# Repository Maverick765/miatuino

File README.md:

# Miatuino ECU NA6 PNP

MiatuinoはSpeeduinoをベースとしたNA6ロードスター専用ECUプロジェクトです。

Speeduino MX-5 PNPモデルをベースとし、部品の入手性、組み立てやすさなどを改善しました。

基本的な技術情報については公式のWikiを参照してください。
https://wiki.speeduino.com

また、部品に関してはできる限り日本国内で入手しやすいものにしています。国内で入手できないものはAliexpressやLCSCで入手可能です。

---

## 対応車種

- 車種：ユーノス・ロードスター（NA6CE）
- 年式：1989年〜1995年
- エンジン：1.6L B6ZE(RS)

注意：NA8には対応していません。

---

## Speeduinoからの変更点

- Arduino Mega2560をMega2560 Proに変更
- SMD部品を減らし、手はんだで組み立てやすいように変更
- A/C制御回路の追加
- 電源回路をROHM製のDC-DCコンバータBP5293-50に変更
- MAPセンサをBOSCH製0 281 002 593に変更

---

## 注意事項

- 仕様はほぼSpeeduinoと同様です。詳細仕様は [Speeduino公式Wiki](https://wiki.speeduino.com/) を参照してください。
- 純正には**吸気温センサー（IAT）が存在しない**ため、追加設置が必須です。
- ノック制御、スピードセンサーなどには非対応です。

---

## ECUの組み立てと取付に必要なもの

- Miatuino基板  
リポジトリ内のGerberファイルを利用。
- 実装用部品  
リポジトリ内の部品表を参照。
- 吸気温センサー(IAT)  
品番：25036751  
エアフロメーターを外したカプラに接続します。  
Aliexpressなどで入手可能
- 吸気温センサー用カプラ  
Aliexpressで「7pin Automotive Connector」などと検索すれば見つかります。
- スロットルポジションセンサー(TPS)  
品番：0280122001  
カプラの形状と配線が純正と同じため、そのまま利用できます。  
Aliexpressなどで入手可能。
- スロットルポジションセンサー用マウントアダプター  
リポジトリ内の.stlファイルを利用。  
3Dプリンタで出力するか、3Dプリントサービスを利用してください。  
.stlファイルは以下のページからも入手可能です。  
[1.6 Miata Kia type tps adapter M5 nuts](https://www.thingiverse.com/thing:4611603)
- MAPセンサー  
0 281 002 593  
Aliexpressなどで入手可能。
- MAPセンサー用カプラー  
品番：1928403966  
Aliexpressなどで入手可能。
- 基板用ケース  
基板のサイズは100mm x 100mmです。適当なサイズのアルミケースに入れます。
- 基板用USB Type Cコネクタ  
ケース内のMega 2560 Proと接続するためのパネルマウントのType Cコネクタ。
- 内径4.5mmのホース   
3m程度。キジマのガソリンホースがおススメです。
- TunerStudio  
[公式ページ](https://www.efianalytics.com/TunerStudio/)から入手可能。
- SpeedyLoader  
[公式ページ](https://speeduino.com/home/support/downloads)から入手可能。

---

## 製作

基本的にはKiCADのプロジェクトや部品表を見ながらはんだ付けすればOKです。
MAPセンサーは基板の3ピンコネクタにカプラを介して取り付けます。

---

## ファームウェアの書き込み

SpeedyLoaderを利用してファームウェアを書き込みます。
[SpeedyLoaderの公式マニュアル](https://wiki.speeduino.com/en/Installing_Firmware)を参考にしてください。

また、書き込みが完了したらbase tuneをダウンロードしておきます。

---

## 取付手順

### スロットルポジションセンサーを交換する

純正のスロットルポジションセンサーを外し、新しいスロットルポジションセンサーをアダプターを利用して取り付けます。

なお、純正のセンサーを取り外すには、スロットルボディーを外す必要があります。
(純正のセンサーを破壊すればスロットルボディーを外さずに新しいセンサーを取り付けることも可能ですがおススメしません)

### エアフロメーターのカプラを外して吸気温センサーを取り付ける

エアフロメータにつながっている7ピンのカプラを外し、吸気温センサを取り付けます。

### ST-SIGのヒューズを外す

エンジンルーム内の運転席側のヒューズボックスを開け、ST-SIGのヒューズを外します。
なお、Miatuinoを利用する場合、このヒューズは常に外したままにしておく必要があります。

_ST-SIGのヒューズは、セルモーターを回している間、一時的に燃料ポンプを動かすための電源が来ているヒューズです。_
_純正状態のNA6では、燃料ポンプの電源ON/OFFをフラップ式のエアフロメータの中にある機械式の接点で行っています。つまり、エンジンが回って負圧が発生している状態でないと燃料ポンプは作動しません。_
_エンジン始動時は負圧が弱く、この接点が動かないため、一時的に燃料ポンプに電源を供給する必要があります。その電源が来ているのがST-SIGのヒューズです。_
_Miatuinoでは、エアフロメータの配線を流用して燃料ポンプの制御を行うことになりますが、この時、ST-SIGのヒューズを残したままにしていると、キーを回したときに基板のドライバICに電流が逆流し、基板が焼けます。_

### 純正ECUを取り外す

助手席側スカッフプレート、一部のトリムを外してカーペットをめくります。
スチールのカバーパネルを外すと、ステーで固定されたECUが見えるので取り外し、カプラーを外します。

### MAPセンサーへつなぐホースを通す

MiatuinoではDジェトロニック方式になるため、インテークマニホールドの負圧をホースでECUまで接続する必要があります。
純正のインテークマニホールドには、ゴムキャップが付いた使われていない負圧取り出しニップルがあるので、それを利用します。
また、ロードスターのエンジンルーム隔壁にはゴム栓でメクラされた穴があるので、その栓を外してホースを通します。

カーペットをめくっている間に、エンジンルーム側からホースを送り、室内側の足元まで届かせます。
室内と反対側のホースの先をインマニにあるニップルに取り付けます。

### Miatuinoを取り付ける

純正ECUを取り外したカプラと、先ほど通したホースをMiatuinoに繋ぎます。
ECUのセッティングやトラブルシューティングのためにも、ECUは元の場所に戻さず、助手席足元に転がすなりしておきます。
ECU底面に面ファスナーのテープを取り付け、内装に張り付けておくのもおすすめです。

---

## セットアップ手順

PCとMiatuinoをUSBケーブルで接続し、PCでTuner Studioを起動し、初期データの書き込みと各種センサーのキャリブレーションを行います。

#### 初期データの書き込み

SpeedyLoaderからダウンロードしたbase tuneを書き込みます。

[File] -> [Load Tune(MSQ)]を選択して、SpeedyLoaderでからダウンロードしたbase tuneを書き込みます。

#### TPSのキャリブレーション

[Tools] -> [Calibrate TPS]を選択します。

正しくTPSが接続されていれば、アクセルペダルを踏めば値が変化することを確認できます。

まずはアクセルを完全に戻した状態で[Closed throttle ADC Count]の右の[Get Current]をクリックして、スロットル全閉時の値を取得します。
次に、アクセルを完全に踏み込んだ状態で[Full throttle ADC Count]の右の[Get Current]をクリックして、スロットル前回時の値を取得します。
完了したら[Accept]をクリックします。

この際、センサーの極性(全開で0Vか、全閉で0Vか)で警告が出ることがありますが、そのまま進めればSpeeduino側で勝手に極性を変更してくれます。

#### 水温センサーのキャリブレーション

[Tools] -> [Calibrate Tempereture Sensor]を選択します。

[SensorTable]のプルダウンから[Coolant Tempereture Sensor]を選択します。

[Table Input Solution]が3 Point Therm Generatorになっていることを確認します。

[Common Sensor Values]のプルダウンから[RX7_CLT(S4&S5)]を選択します。

[Write to Controller]をクリックして完了したら[Close]をクリックします。

#### 吸気温センサーのキャリブレーション

[Tools] -> [Calibrate Tempereture Sensor]を選択します。

[SensorTable]のプルダウンから[Air Tempereture Sensor]を選択します。

[Table Input Solution]が3 Point Therm Generatorになっていることを確認します。

[Common Sensor Values]のプルダウンから[RX7_AFM(S5 in AFM)]を選択します。

[Write to Controller]をクリックして完了したら[Close]をクリックします。

#### O2センサーの設定

[Tuning] -> [AFR/O2]を選択します。

純正のO2センサーを利用する場合、[Sensor Type]に[Narrow Band]を指定します。

完了したら[Burn]をクリックして[Close]をクリックします。

純正のO2センサーを利用する場合はこれで完了ですが、社外のワイドバンドセンサーを付けている場合はキャリブレーションを行う必要があります。

[Tools] -> [Calibrate AFR Sensor]を選択します。

[EGO Sensor]のプルダウンメニューから、利用しているセンサーのメーカーを選択します。

[Write to Controller]をクリックして完了したら[Close]をクリックします。

---

## 関連リンク

- [Speeduino 公式サイト（英語）](https://speeduino.com/)
- [Speeduino Wiki（英語）](https://wiki.speeduino.com/en/boards/MX5_PNP)
- [TunerStudio ダウンロードページ](https://www.efianalytics.com/TunerStudio/)
- [Speedy Loader ダウンロードページ](https://speeduino.com/home/support/downloads)
- [1.6 Miata Kia type tps adapter M5 nuts](https://www.thingiverse.com/thing:4611603)

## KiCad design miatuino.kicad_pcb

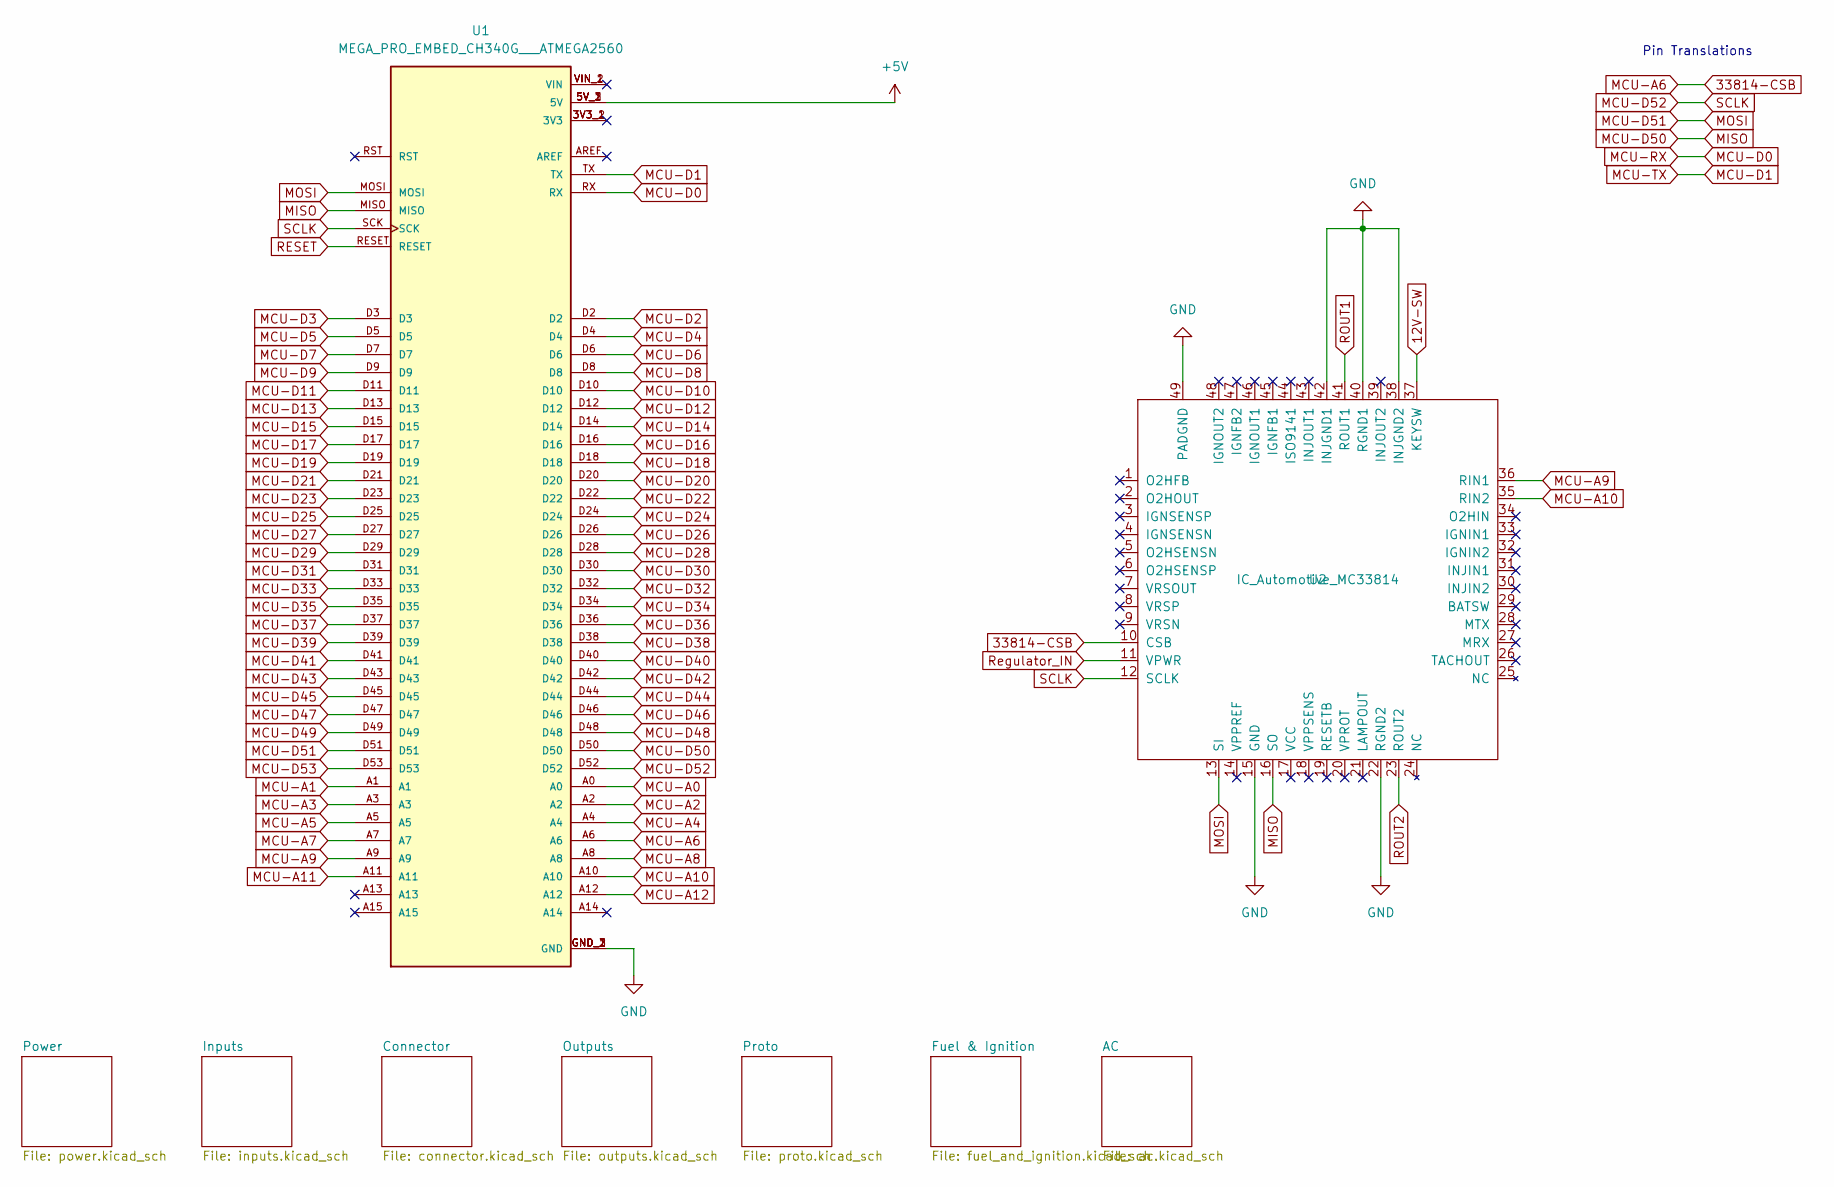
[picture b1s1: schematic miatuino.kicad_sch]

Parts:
U1: MEGA_PRO_EMBED_CH340G___ATMEGA2560; Arduino Mega Pro; PARTREV 12/May/2017
U2: IC_Automotive_MC33814; LQFP-48-1EP_7x7mm_P0.5mm_EP3.6x3.6mm_ThermalVias; Manufacturer_Part_Number MC33814

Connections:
12V-SW: U2.37 (KEYSW); also elsewhere on the board
33814-CSB: U1.A6, U2.10 (CSB)
+5V: U1.5V_1 (5V), U1.5V_2 (5V), U1.5V_3 (5V); also elsewhere on the board
ADC-Clamp-1: U1.A0; also elsewhere on the board
ADC-Clamp-2: U1.A1; also elsewhere on the board
ADC-Clamp-3: U1.A2; also elsewhere on the board
ADC-Clamp-4: U1.A3; also elsewhere on the board
ADC-Clamp-5: U1.A4; also elsewhere on the board
ADC-Clamp-11: U1.D12; also elsewhere on the board
ADC-Clamp-13: U1.D18; also elsewhere on the board
ADC-Clamp-14: U1.D19; also elsewhere on the board
GND: U1.GND_1 (GND), U1.GND_2 (GND), U1.GND_3 (GND), U2.15 (GND), U2.22 (RGND2), U2.38 (INJGND2), U2.40 (RGND1), U2.42 (INJGND1), U2.49 (PADGND); also elsewhere on the board
MCU-A5: U1.A5; also elsewhere on the board
MCU-A7: U1.A7
MCU-A8: U1.A8
MCU-A9: U1.A9, U2.36 (RIN1)
MCU-A10: U1.A10, U2.35 (RIN2)
MCU-A11: U1.A11
MCU-A12: U1.A12; also elsewhere on the board
MCU-D0: U1.RX; also elsewhere on the board
MCU-D1: U1.TX; also elsewhere on the board
MCU-D2: U1.D2; also elsewhere on the board
MCU-D3: U1.D3
MCU-D4: U1.D4; also elsewhere on the board
MCU-D5: U1.D5
MCU-D6: U1.D6
MCU-D7: U1.D7
MCU-D8: U1.D8; also elsewhere on the board
MCU-D9: U1.D9; also elsewhere on the board
MCU-D10: U1.D10; also elsewhere on the board
MCU-D11: U1.D11; also elsewhere on the board
MCU-D13: U1.D13
MCU-D14: U1.D14
MCU-D15: U1.D15
MCU-D16: U1.D16
MCU-D17: U1.D17
MCU-D20: U1.D20; also elsewhere on the board
MCU-D21: U1.D21
MCU-D22: U1.D22
MCU-D23: U1.D23
MCU-D24: U1.D24
MCU-D25: U1.D25
MCU-D26: U1.D26
MCU-D27: U1.D27
MCU-D28: U1.D28
MCU-D29: U1.D29
MCU-D30: U1.D30
MCU-D31: U1.D31
MCU-D32: U1.D32; also elsewhere on the board
MCU-D33: U1.D33; also elsewhere on the board
MCU-D34: U1.D34
MCU-D35: U1.D35; also elsewhere on the board
MCU-D36: U1.D36
MCU-D37: U1.D37; also elsewhere on the board
MCU-D38: U1.D38
MCU-D39: U1.D39; also elsewhere on the board
MCU-D40: U1.D40
MCU-D41: U1.D41; also elsewhere on the board
MCU-D42: U1.D42
MCU-D43: U1.D43
MCU-D44: U1.D44; also elsewhere on the board
MCU-D45: U1.D45
MCU-D46: U1.D46; also elsewhere on the board
MCU-D47: U1.D47
MCU-D48: U1.D48
MCU-D49: U1.D49; also elsewhere on the board
MCU-D50: U1.D50, U1.MISO, U2.16 (SO)
MCU-D51: U1.D51, U1.MOSI, U2.13 (SI)
MCU-D52: U1.D52, U1.SCK, U2.12 (SCLK)
MCU-D53: U1.D53
RESET: U1.RESET; also elsewhere on the board
ROUT1: U2.41 (ROUT1); also elsewhere on the board
ROUT2: U2.23 (ROUT2)
Regulator_IN: U2.11 (VPWR); also elsewhere on the board

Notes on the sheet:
Pin Translations

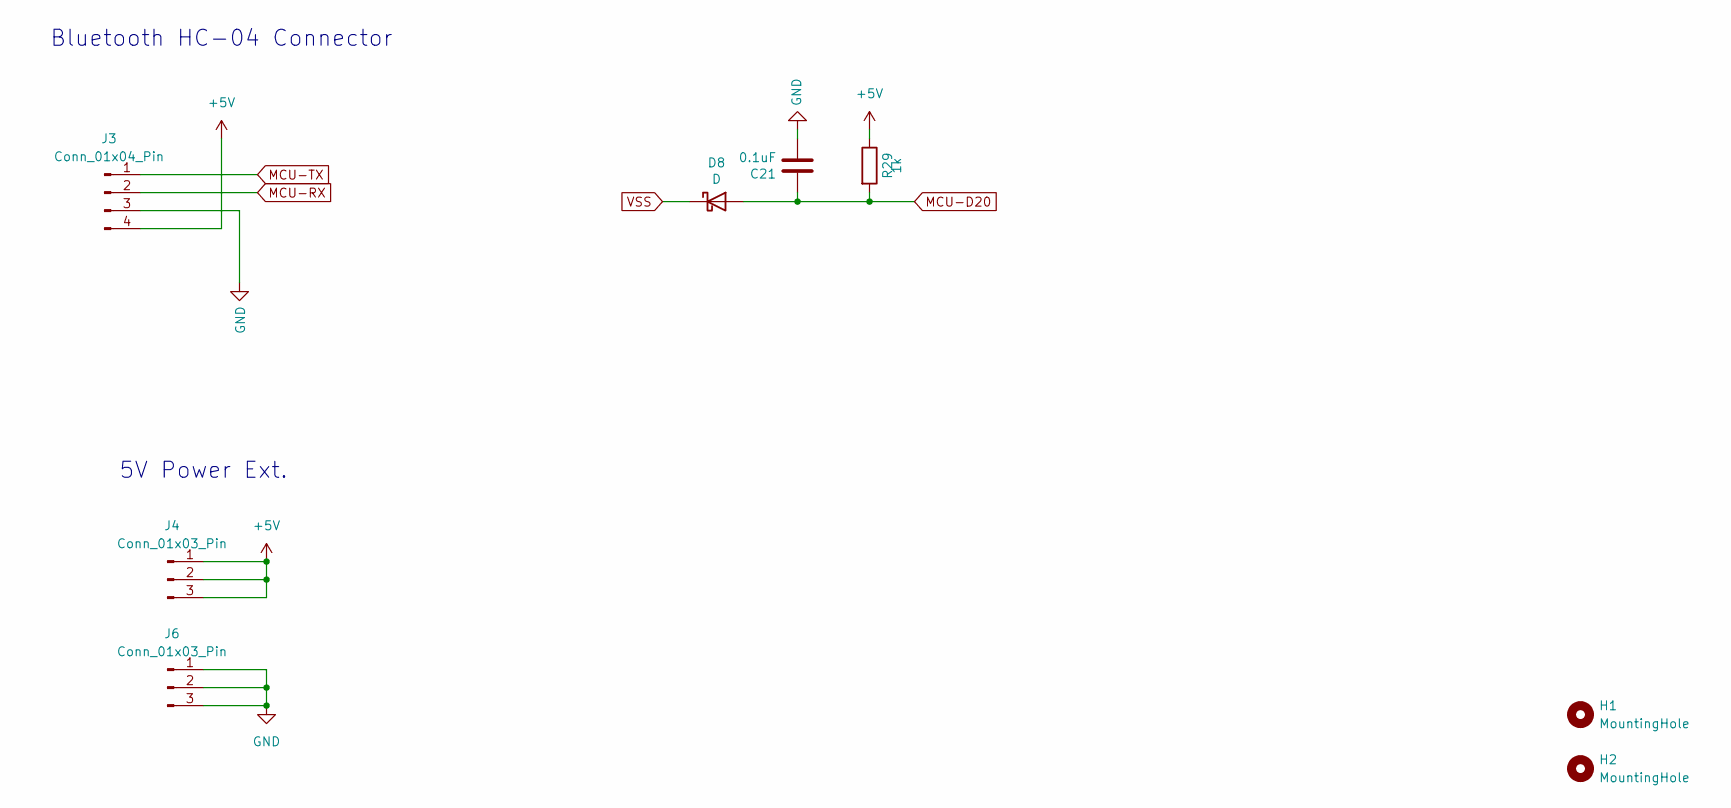
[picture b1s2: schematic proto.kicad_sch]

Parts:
C21: 0.1uF; C_Disc_D4.7mm_W2.5mm_P5.00mm; Manufacturer_Part_Number CC0805KRX7R9BB104; Digikey Part Number 311-1140-1-ND
D8: D; D_T-1_P5.08mm_Horizontal; Manufacturer_Part_Number 1N4448WX-TP; Digikey Part Number 1N4448WXTPMSCT-ND
H1, H2: MountingHole; MountingHole_3.2mm_M3_DIN965_Pad
J3: Conn_01x04_Pin; PinSocket_1x04_P2.54mm_Vertical
J4, J6: Conn_01x03_Pin; PinHeader_1x03_P2.54mm_Vertical
R29: 1k; R_Axial_DIN0207_L6.3mm_D2.5mm_P7.62mm_Horizontal; Manufacturer_Part_Number RC0805FR-071KL; Digikey Part Number 311-1.00KCRCT-ND

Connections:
+5V: J3.4, J4.1, J4.2, J4.3, R29.1; also elsewhere on the board
GND: C21.2, J3.3, J6.1, J6.2, J6.3; also elsewhere on the board
MCU-D0: J3.2; also elsewhere on the board
MCU-D1: J3.1; also elsewhere on the board
MCU-D20: C21.1, D8.2 (A), R29.2; also elsewhere on the board
VSS: D8.1 (K); also elsewhere on the board

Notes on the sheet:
Bluetooth HC-04 Connector
5V Power Ext.

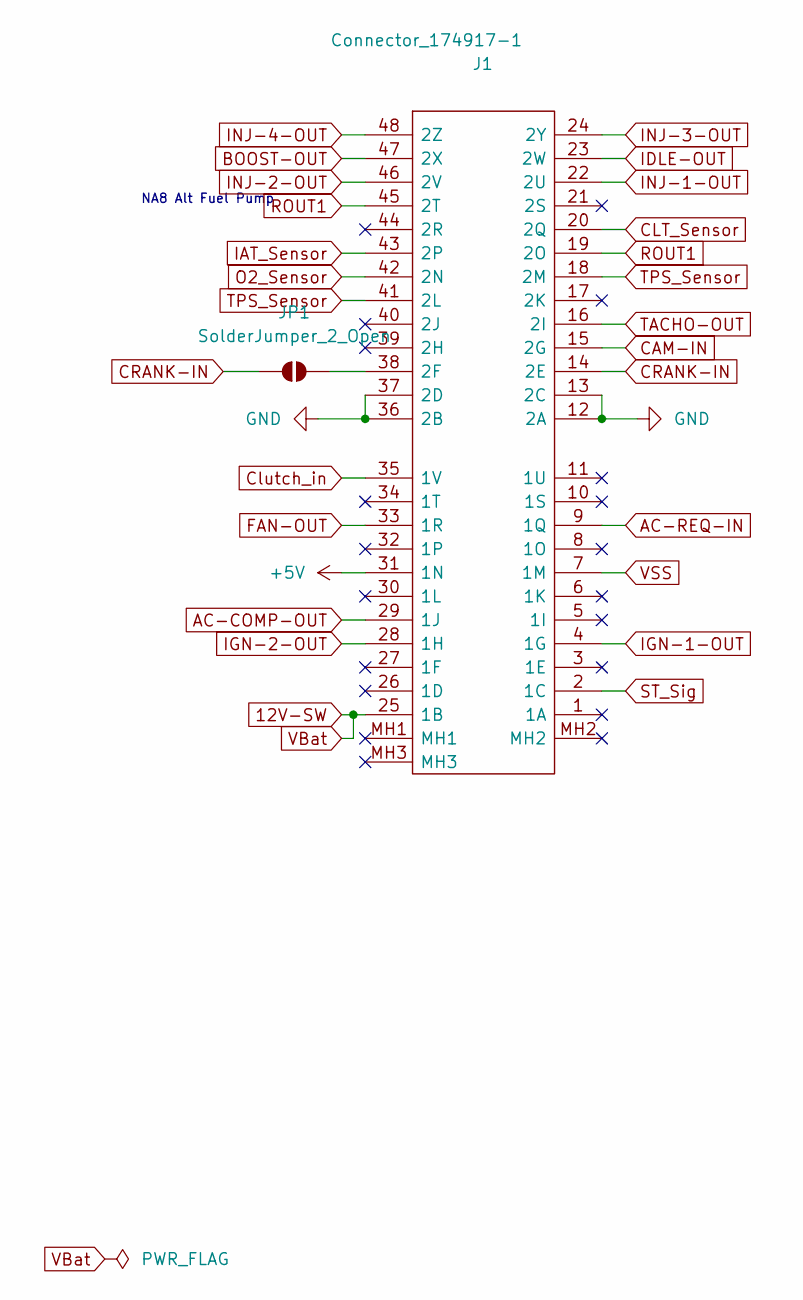
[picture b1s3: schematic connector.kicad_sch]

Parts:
J1: Connector_174917-1; 1749171; Manufacturer_Part_Number 174917-1
JP1: SolderJumper_2_Open; SolderJumper-2_P1.3mm_Open_RoundedPad1.0x1.5mm

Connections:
12V-SW: J1.25 (1B); also elsewhere on the board
+5V: J1.31 (1N); also elsewhere on the board
AC-COMP-OUT: J1.29 (1J); also elsewhere on the board
AC-REQ-IN: J1.9 (1Q); also elsewhere on the board
BOOST-OUT: J1.47 (2X); also elsewhere on the board
CAM-IN: J1.15 (2G); also elsewhere on the board
CLT_Sensor: J1.20 (2Q); also elsewhere on the board
CRANK-IN: J1.14 (2E), JP1.1 (A); also elsewhere on the board
Clutch_in: J1.35 (1V); also elsewhere on the board
FAN-OUT: J1.33 (1R); also elsewhere on the board
GND: J1.12 (2A), J1.13 (2C), J1.36 (2B), J1.37 (2D); also elsewhere on the board
IAT_Sensor: J1.43 (2P); also elsewhere on the board
IDLE-OUT: J1.23 (2W); also elsewhere on the board
IGN-1-OUT: J1.4 (1G); also elsewhere on the board
IGN-2-OUT: J1.28 (1H); also elsewhere on the board
INJ-1-OUT: J1.22 (2U); also elsewhere on the board
INJ-2-OUT: J1.46 (2V); also elsewhere on the board
INJ-3-OUT: J1.24 (2Y); also elsewhere on the board
INJ-4-OUT: J1.48 (2Z); also elsewhere on the board
unnamed: J1.38 (2F), JP1.2 (B)
O2_Sensor: J1.42 (2N); also elsewhere on the board
ROUT1: J1.19 (2O), J1.45 (2T); also elsewhere on the board
ST_Sig: J1.2 (1C); also elsewhere on the board
TACHO-OUT: J1.16 (2I); also elsewhere on the board
TPS_Sensor: J1.18 (2M), J1.41 (2L); also elsewhere on the board
VSS: J1.7 (1M); also elsewhere on the board

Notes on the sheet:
NA8 Alt Fuel Pump

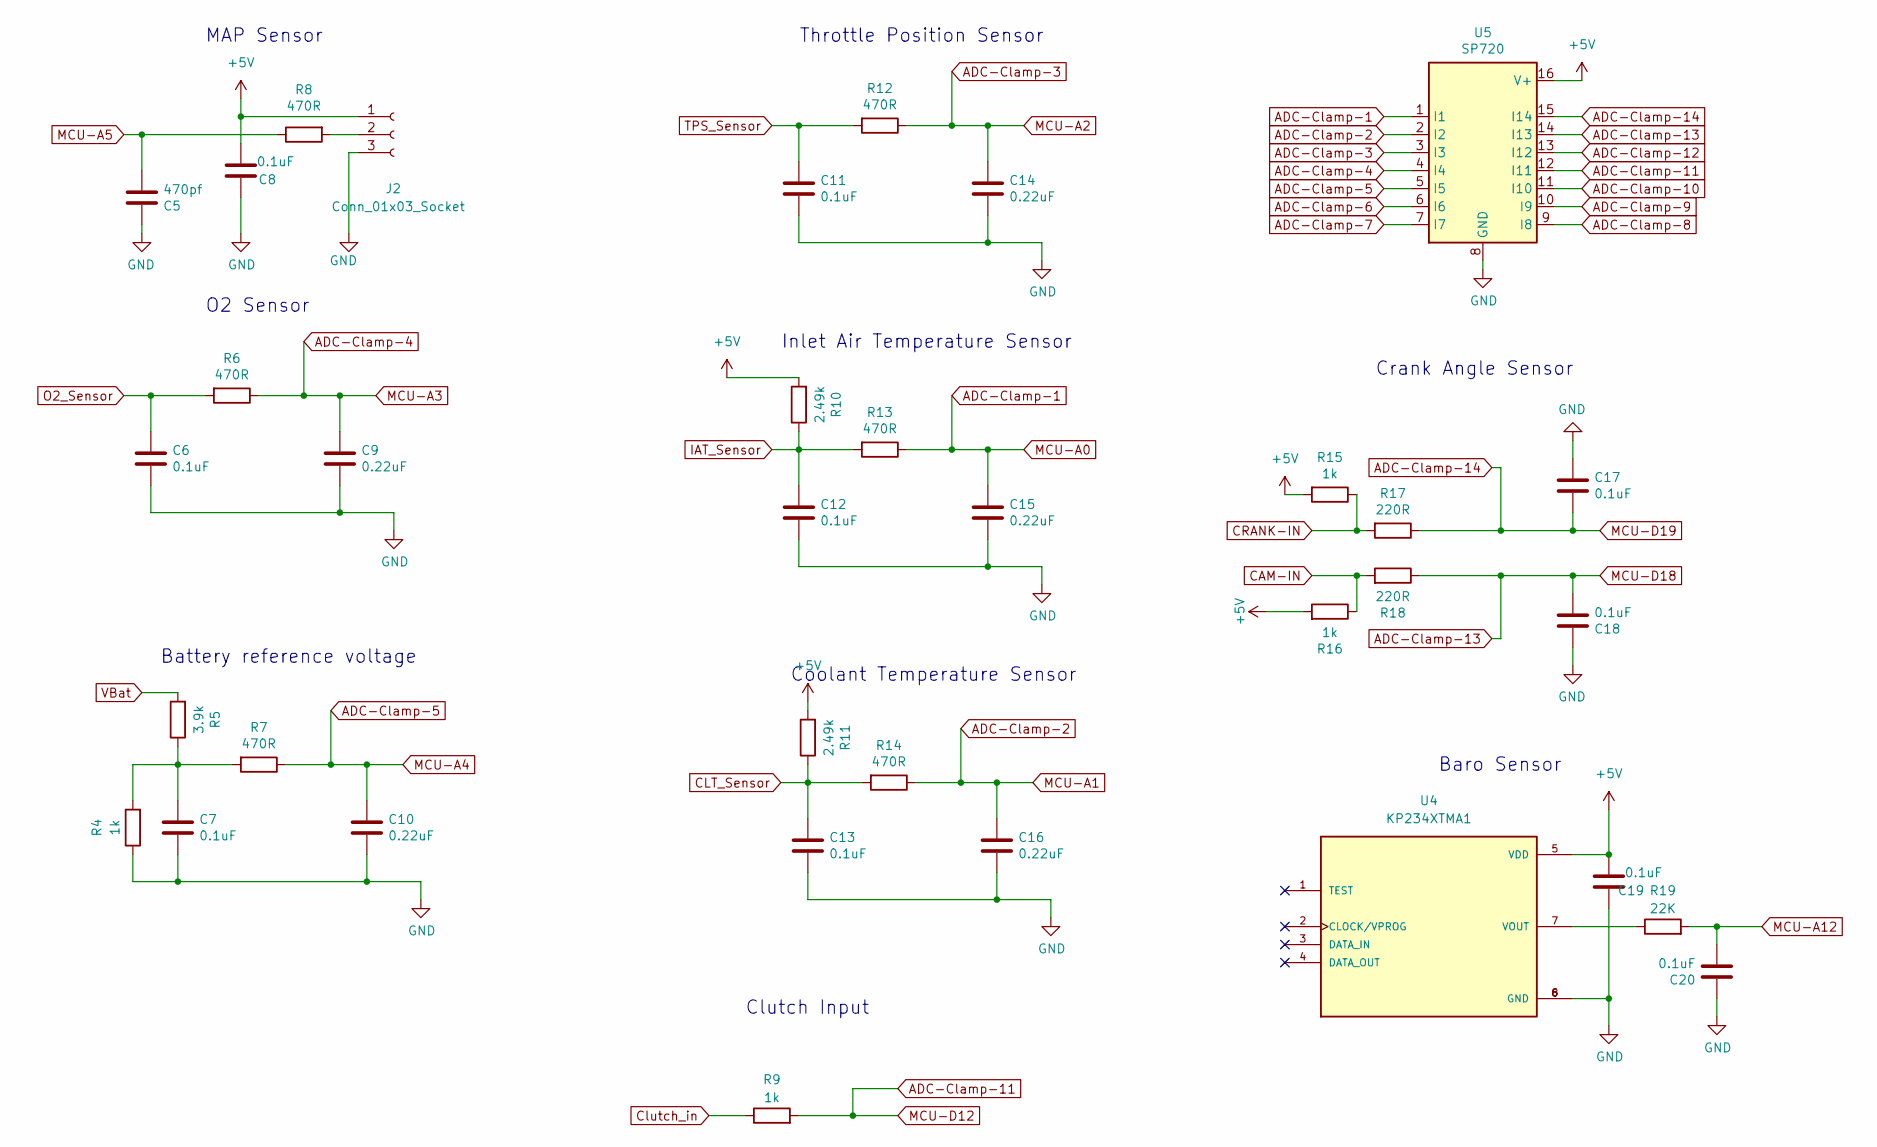
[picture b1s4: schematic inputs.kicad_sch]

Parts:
C5: 470pf; C_Disc_D4.7mm_W2.5mm_P5.00mm; Part # CC0805KRX7R9BB471; Digikey Part Number 311-1124-1-ND
C6, C7, C12, C13, C17, C18, C20: 0.1uF; C_Disc_D4.7mm_W2.5mm_P5.00mm; Manufacturer_Part_Number CC0805KRX7R9BB104; Digikey Part Number 311-1140-1-ND
C8: 0.1uF; C_Disc_D4.7mm_W2.5mm_P5.00mm; Part # CC0805KRX7R9BB103; Digikey Part Number 311-1136-1-ND
C9, C10, C14, C15, C16: 0.22uF; C_Disc_D4.7mm_W2.5mm_P5.00mm; Manufacturer_Part_Number CL21B224KOCNNNC; Digikey Part Number 1276-1284-1-ND
C11: 0.1uF; C_Disc_D4.7mm_W2.5mm_P5.00mm; Part # CC0805KRX7R9BB104; Digikey Part Number 311-1140-1-ND
C19: 0.1uF; C_Disc_D4.7mm_W2.5mm_P5.00mm; Manufacturer_Part_Number CC0805KRX7R9BB103; Digikey Part Number 311-1136-1-ND
J2: Conn_01x03_Socket; FanPinHeader_1x03_P2.54mm_Vertical
R4, R9, R15, R16: 1k; R_Axial_DIN0207_L6.3mm_D2.5mm_P7.62mm_Horizontal; Manufacturer_Part_Number RC0805FR-071KL; Digikey Part Number 311-1.00KCRCT-ND
R5: 3.9k; R_Axial_DIN0207_L6.3mm_D2.5mm_P7.62mm_Horizontal; Manufacturer_Part_Number RC0805FR-073K9L; Digikey Part Number 311-3.90KCRCT-ND
R6, R7, R12, R13, R14: 470R; R_Axial_DIN0207_L6.3mm_D2.5mm_P7.62mm_Horizontal; Manufacturer_Part_Number ERJ-6ENF4700V; Digikey Part Number P470CCT-ND
R8: 470R; R_Axial_DIN0207_L6.3mm_D2.5mm_P7.62mm_Horizontal; Part # ERJ-6ENF4700V; Digikey Part Number P470CCT-ND
R10, R11: 2.49k; R_Axial_DIN0207_L6.3mm_D2.5mm_P7.62mm_Horizontal; Manufacturer_Part_Number RT0805BRD072K49L; Digikey Part Number YAG1854CT-ND
R17, R18: 220R; R_Axial_DIN0207_L6.3mm_D2.5mm_P7.62mm_Horizontal; Manufacturer_Part_Number RC0805FR-07220RL; Digikey Part Number 311-220CRCT-ND
R19: 22K; R_Axial_DIN0207_L6.3mm_D2.5mm_P7.62mm_Horizontal; Manufacturer_Part_Number AC0805JR-0722KL; Digikey Part Number YAG3773CT-ND
U4: KP234XTMA1; XDCR_KP234XTMA1; PARTREV 1.0
U5: SP720; SOIC-16_3.9x9.9mm_P1.27mm; Manufacturer_Part_Number SP720ABTG; Digikey Part Number F3162CT-ND

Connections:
12V-SW: R5.2; also elsewhere on the board
+5V: C8.2, C19.2, J2.1, R10.2, R11.2, R15.2, R16.2, U4.5 (VDD), U5.16 (V+); also elsewhere on the board
ADC-Clamp-1: C15.1, R13.1, U5.1 (I1); also elsewhere on the board
ADC-Clamp-2: C16.1, R14.1, U5.2 (I2); also elsewhere on the board
ADC-Clamp-3: C14.1, R12.1, U5.3 (I3); also elsewhere on the board
ADC-Clamp-4: C9.1, R6.1, U5.4 (I4); also elsewhere on the board
ADC-Clamp-5: C10.1, R7.1, U5.5 (I5); also elsewhere on the board
ADC-Clamp-6: U5.6 (I6)
ADC-Clamp-7: U5.7 (I7)
ADC-Clamp-8: U5.9 (I8)
ADC-Clamp-9: U5.10 (I9)
ADC-Clamp-10: U5.11 (I10)
ADC-Clamp-11: R9.2, U5.12 (I11); also elsewhere on the board
ADC-Clamp-12: U5.13 (I12)
ADC-Clamp-13: C18.2, R18.1, U5.14 (I13); also elsewhere on the board
ADC-Clamp-14: C17.2, R17.1, U5.15 (I14); also elsewhere on the board
CAM-IN: R16.1, R18.2; also elsewhere on the board
CLT_Sensor: C13.1, R11.1, R14.2; also elsewhere on the board
CRANK-IN: R15.1, R17.2; also elsewhere on the board
Clutch_in: R9.1; also elsewhere on the board
GND: C5.1, C6.2, C7.2, C8.1, C9.2, C10.2, C11.2, C12.2, C13.2, C14.2, C15.2, C16.2, C17.1, C18.1, C19.1, C20.1, J2.3, R4.1, U4.6 (GND), U4.8 (GND), U5.8 (GND); also elsewhere on the board
IAT_Sensor: C12.1, R10.1, R13.2; also elsewhere on the board
MCU-A5: C5.2, R8.1; also elsewhere on the board
MCU-A12: C20.2, R19.2; also elsewhere on the board
unnamed: C7.1, R4.2, R5.1, R7.2
unnamed: J2.2, R8.2
unnamed: R19.1, U4.7 (VOUT)
O2_Sensor: C6.1, R6.2; also elsewhere on the board
TPS_Sensor: C11.1, R12.2; also elsewhere on the board

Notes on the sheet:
O2 Sensor
Coolant Temperature Sensor
Clutch Input
Crank Angle Sensor
Baro Sensor
Throttle Position Sensor
MAP Sensor
Battery reference voltage
Inlet Air Temperature Sensor

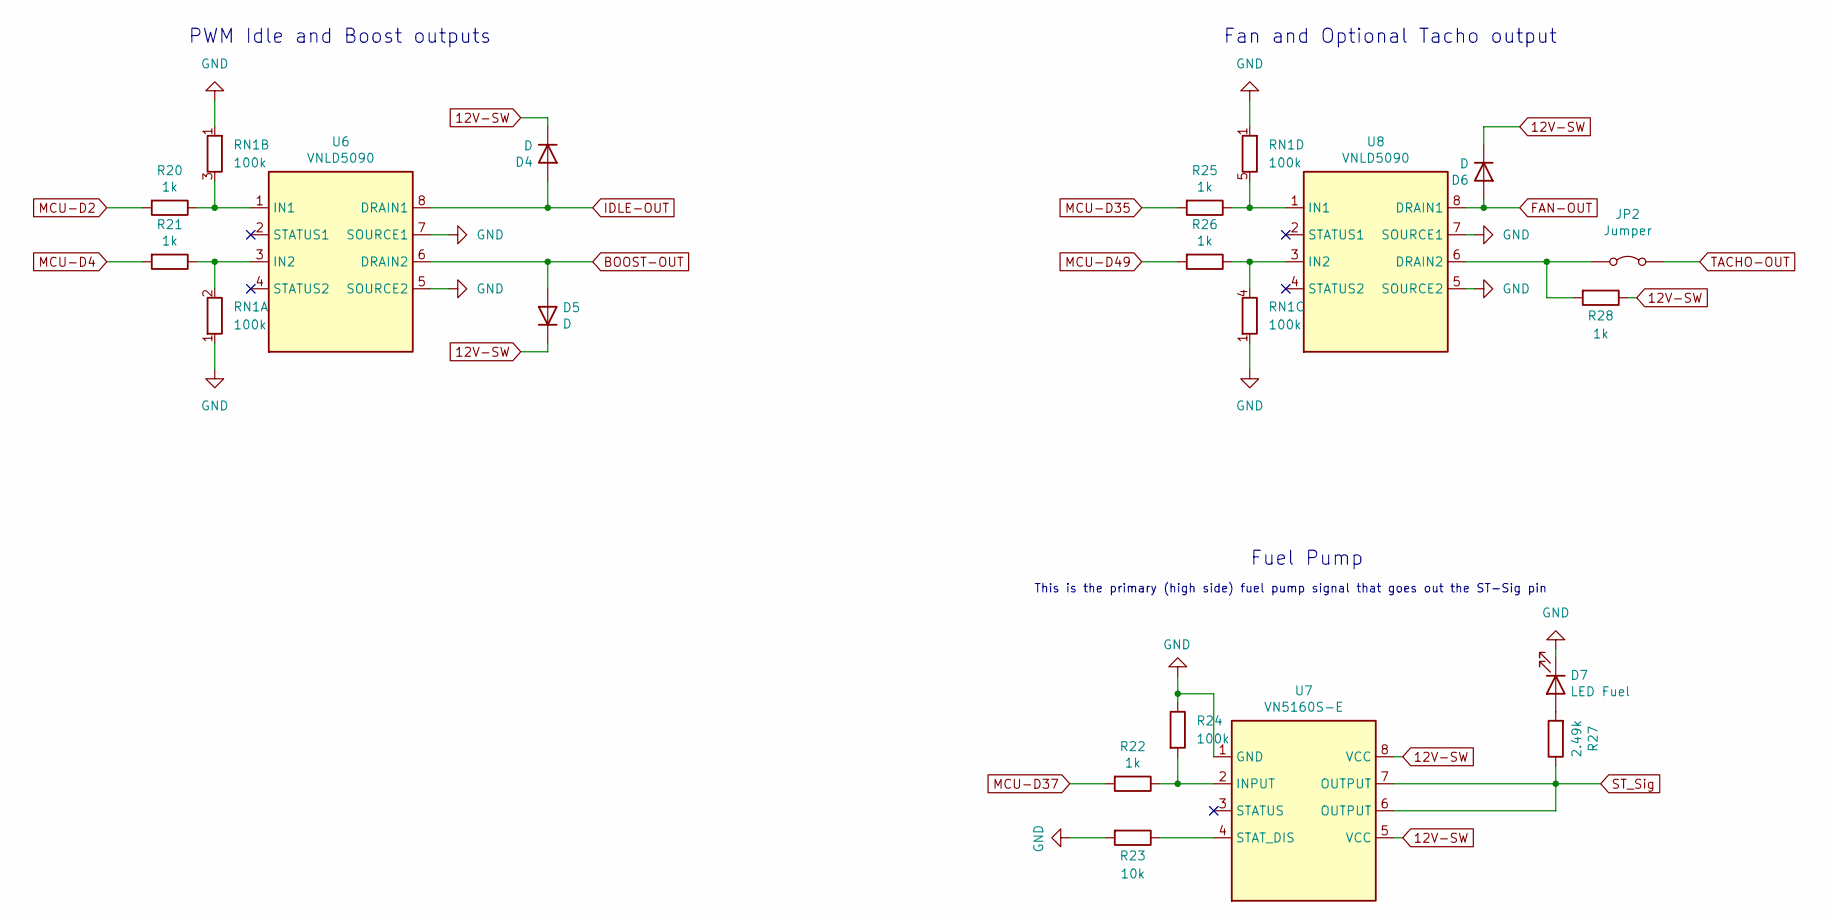
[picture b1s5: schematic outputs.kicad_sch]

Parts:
D4, D5, D6: D; D_DO-41_SOD81_P7.62mm_Horizontal; Manufacturer_Part_Number NBRS2H100T3G; Digikey Part Number NBRS2H100T3GTR-ND
D7: LED Fuel; LED_D3.0mm; Manufacturer_Part_Number LH R974-LP-1; Digikey Part Number 475-1415-1-ND
JP2: Jumper; SolderJumper-2_P1.3mm_Open_RoundedPad1.0x1.5mm
R20, R21, R22, R25, R26, R28: 1k; R_Axial_DIN0207_L6.3mm_D2.5mm_P7.62mm_Horizontal; Manufacturer_Part_Number RC0805FR-071KL; Digikey Part Number 311-1.00KCRCT-ND
R23: 10k; R_Axial_DIN0207_L6.3mm_D2.5mm_P7.62mm_Horizontal; Manufacturer_Part_Number RC0805JR-0710KL; Digikey Part Number 311-10KARCT-ND
R24: 100k; R_Axial_DIN0207_L6.3mm_D2.5mm_P7.62mm_Horizontal
R27: 2.49k; R_Axial_DIN0207_L6.3mm_D2.5mm_P7.62mm_Horizontal; Manufacturer_Part_Number RT0805BRD072K49L; Digikey Part Number YAG1854CT-ND
RN1: 100k; R_Array_SIP5
U6, U8: VNLD5090; SO-8_3.9x4.9mm_P1.27mm; Manufacturer_Part_Number VNLD5090-E; Digikey Part Number 497-18682-ND
U7: VN5160S-E; SO-8_3.9x4.9mm_P1.27mm; Manufacturer_Part_Number VN5160S-E; Digikey Part Number 497-19720-ND

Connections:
12V-SW: D4.1 (K), D5.1 (K), D6.1 (K), R28.1, U7.5 (VCC), U7.8 (VCC); also elsewhere on the board
BOOST-OUT: D5.2 (A), U6.6 (DRAIN2); also elsewhere on the board
FAN-OUT: D6.2 (A), U8.8 (DRAIN1); also elsewhere on the board
GND: D7.1 (K), R23.2, R24.1, RN1.1 (R1), U6.5 (SOURCE2), U6.7 (SOURCE1), U7.1 (GND), U8.5 (SOURCE2), U8.7 (SOURCE1); also elsewhere on the board
IDLE-OUT: D4.2 (A), U6.8 (DRAIN1); also elsewhere on the board
MCU-D2: R20.2; also elsewhere on the board
MCU-D4: R21.2; also elsewhere on the board
MCU-D35: R25.2; also elsewhere on the board
MCU-D37: R22.2; also elsewhere on the board
MCU-D49: R26.2; also elsewhere on the board
unnamed: D7.2 (A), R27.2
unnamed: JP2.1 (A), R28.2, U8.6 (DRAIN2)
unnamed: R21.1, RN1.2 (R1.2), U6.3 (IN2)
unnamed: R20.1, RN1.3 (R2.2), U6.1 (IN1)
unnamed: R26.1, RN1.4 (R3.2), U8.3 (IN2)
unnamed: R25.1, RN1.5 (R4.2), U8.1 (IN1)
unnamed: R22.1, R24.2, U7.2 (INPUT)
unnamed: R23.1, U7.4 (STAT_DIS)
ST_Sig: R27.1, U7.6 (OUTPUT), U7.7 (OUTPUT); also elsewhere on the board
TACHO-OUT: JP2.2 (B); also elsewhere on the board

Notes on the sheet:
Fan and Optional Tacho output
PWM Idle and Boost outputs
This is the primary (high side) fuel pump signal that goes out the ST-Sig pin
Fuel Pump

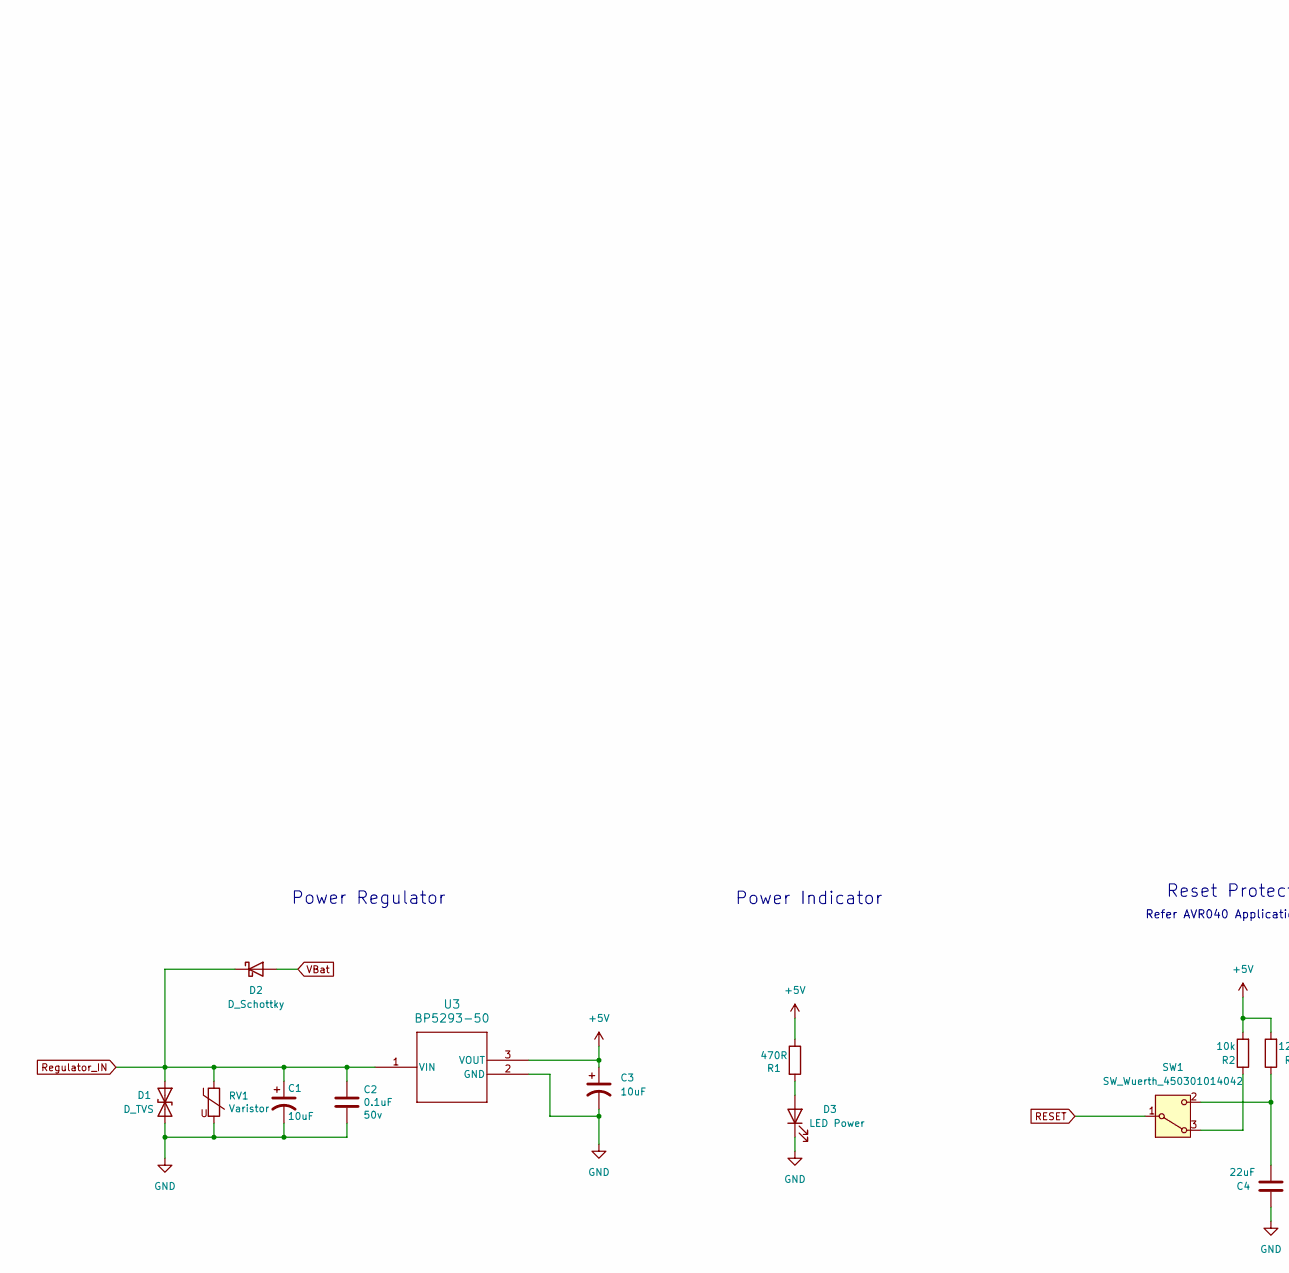
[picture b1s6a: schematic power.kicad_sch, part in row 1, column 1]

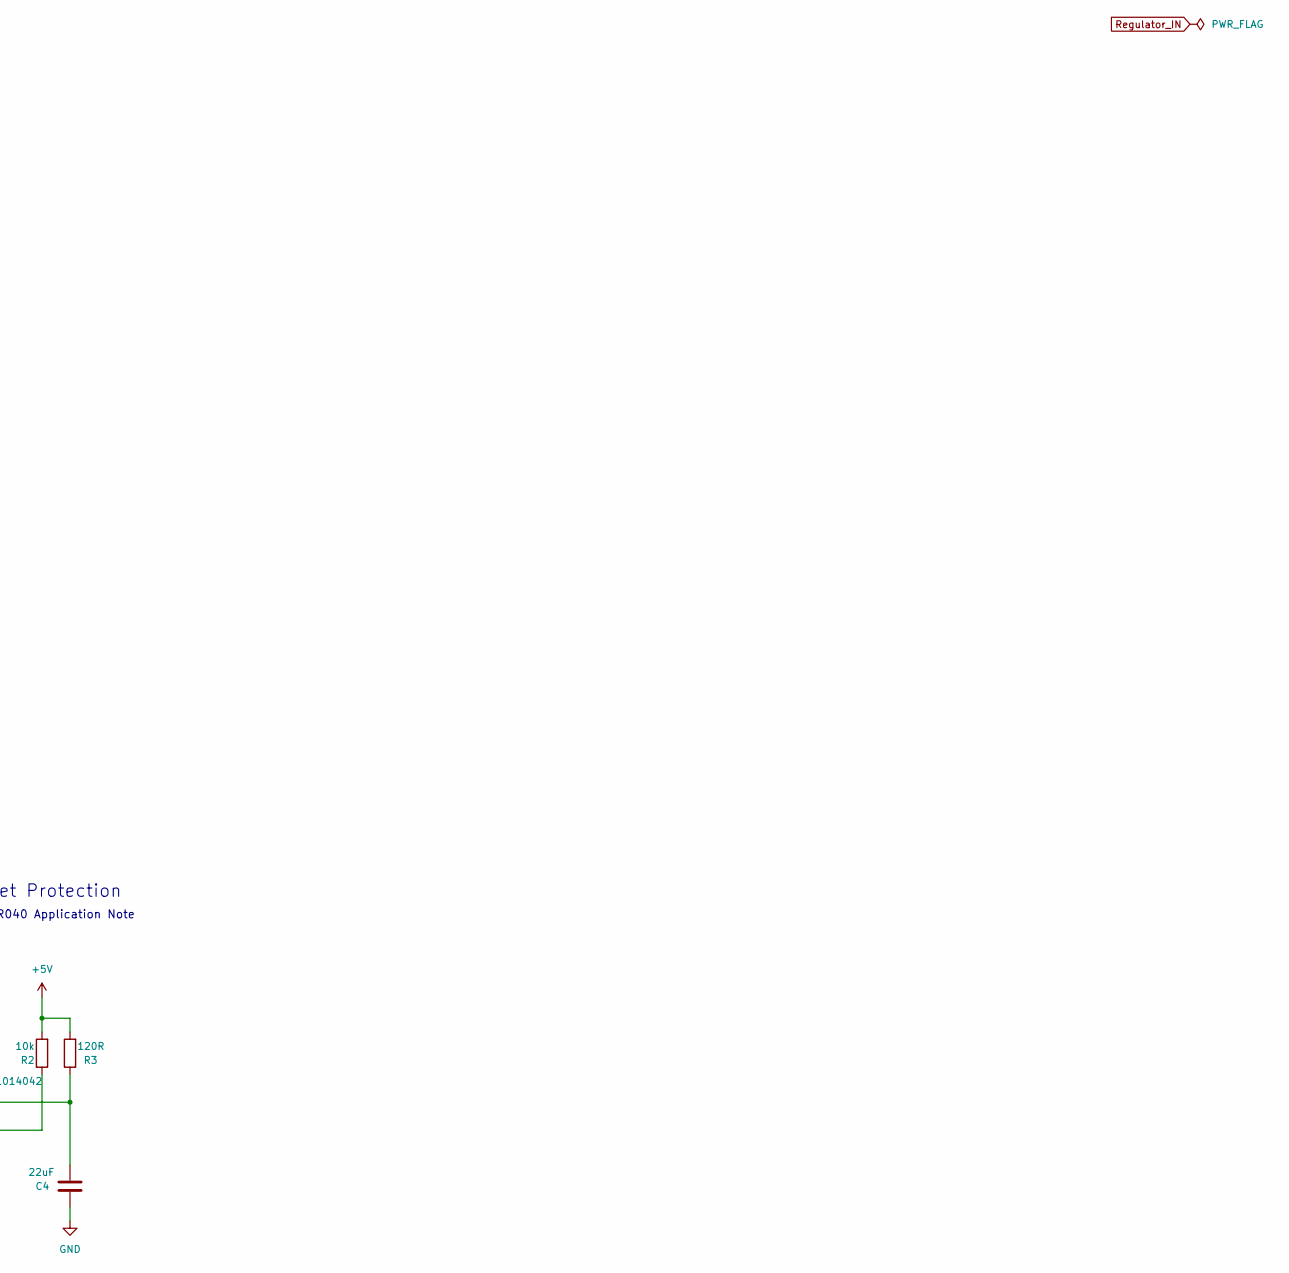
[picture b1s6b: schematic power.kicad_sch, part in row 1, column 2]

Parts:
C1: 10uF; CP_Radial_D5.0mm_P2.00mm; Voltage 35v; Manufacturer_Part_Number T491D106K050AT; Digikey Part Number 399-8361-1-ND
C2: 0.1uF; C_Disc_D4.7mm_W2.5mm_P5.00mm; Voltage 50v; Manufacturer_Part_Number C1206C104K5RAC7867; Digikey Part Number 399-1249-1-ND
C3: 10uF; CP_Radial_D5.0mm_P2.00mm
C4: 22uF; C_Disc_D4.7mm_W2.5mm_P5.00mm; Manufacturer_Part_Number CL21A226KQCLRNC; Digikey Part Number 1276-6687-1-ND
D1: D_TVS; D_DO-41_SOD81_P7.62mm_Horizontal
D2: D_Schottky; D_DO-41_SOD81_P7.62mm_Horizontal; Manufacturer_Part_Number 1N5818-TP; Digikey Part Number 1N5818-TPCT-ND
D3: LED Power; LED_D3.0mm; Manufacturer_Part_Number LG R971-KN-1; Digikey Part Number 475-1410-1-ND
R1: 470R; R_Axial_DIN0207_L6.3mm_D2.5mm_P7.62mm_Horizontal; Manufacturer_Part_Number ERJ-6ENF4700V; Digikey Part Number P470CCT-ND
R2: 10k; R_Axial_DIN0207_L6.3mm_D2.5mm_P7.62mm_Horizontal; Manufacturer_Part_Number RC0805JR-0710KL; Digikey Part Number 311-10KARCT-ND
R3: 120R; R_Axial_DIN0207_L6.3mm_D2.5mm_P7.62mm_Horizontal; Manufacturer_Part_Number RC0805FR-07120RL; Digikey Part Number 311-120CRCT-ND
RV1: Varistor; RV_Disc_D15.5mm_W4.7mm_P7.5mm; Manufacturer_Part_Number MOV-14D220K; Digikey Part Number MOV-14D220K-ND
SW1: SW_Wuerth_450301014042; SW_Slide-03_Wuerth-WS-SLTV_10x2.5x6.4_P2.54mm
U3: BP5293-50

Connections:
12V-SW: D2.2 (A); also elsewhere on the board
+5V: C3.1, R1.1, R2.2, R3.2, U3.3 (VOUT); also elsewhere on the board
GND: C1.2, C2.2, C3.2, C4.2, D1.2 (A2), D3.1 (K), RV1.2, U3.2 (GND); also elsewhere on the board
unnamed: D3.2 (A), R1.2
unnamed: R2.1, SW1.3 (A)
unnamed: C4.1, R3.1, SW1.2 (C)
RESET: SW1.1 (B); also elsewhere on the board
Regulator_IN: C1.1, C2.1, D1.1 (A1), D2.1 (K), RV1.1, U3.1 (VIN); also elsewhere on the board

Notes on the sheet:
Power Regulator
Refer AVR040 Application Note
Power Indicator
Reset Protection

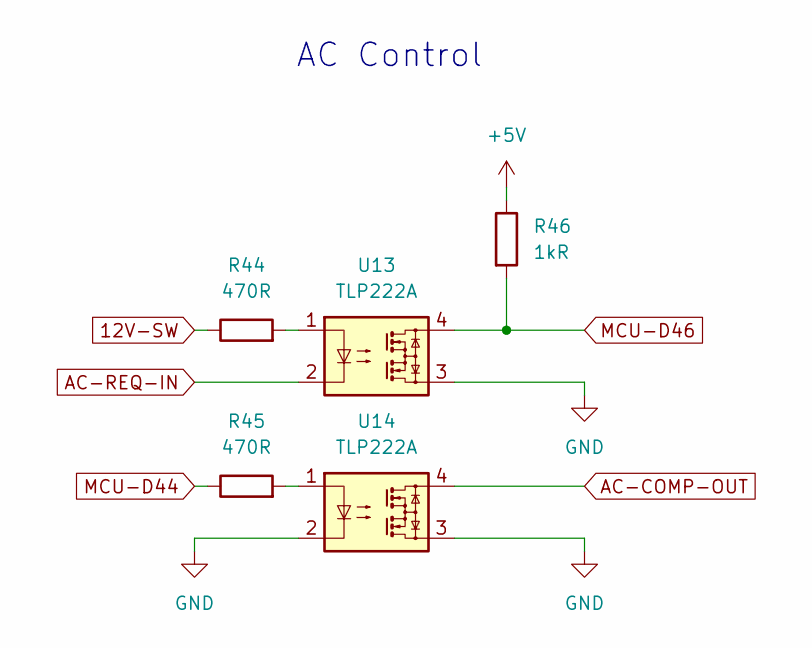
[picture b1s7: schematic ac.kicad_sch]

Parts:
R44, R45: 470R; R_Axial_DIN0207_L6.3mm_D2.5mm_P7.62mm_Horizontal
R46: 1kR; R_Axial_DIN0207_L6.3mm_D2.5mm_P7.62mm_Horizontal
U13, U14: TLP222A; DIP-4_W7.62mm

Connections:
12V-SW: R44.1; also elsewhere on the board
+5V: R46.1; also elsewhere on the board
AC-COMP-OUT: U14.4; also elsewhere on the board
AC-REQ-IN: U13.2; also elsewhere on the board
GND: U13.3, U14.2, U14.3; also elsewhere on the board
MCU-D44: R45.1; also elsewhere on the board
MCU-D46: R46.2, U13.4; also elsewhere on the board
unnamed: R44.2, U13.1
unnamed: R45.2, U14.1

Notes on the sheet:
AC Control
